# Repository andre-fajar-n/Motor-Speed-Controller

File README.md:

# motor-speed-controller
This is my answer for job test for Electrical Embedded Engineer position from a company. The task is to make motor speed controller used ATMega 328, and trasnfer the data to ESP wroom 02 to save in microSD card and web server

# Schematic Design
 
Or you can see the PDF in folder `Schematic`

# PCB Design
### Design for all layer

### Design for top layer

### Design for bottom layer

# Firmware
For firmware, I used Arduino programming to both of the microcontroller

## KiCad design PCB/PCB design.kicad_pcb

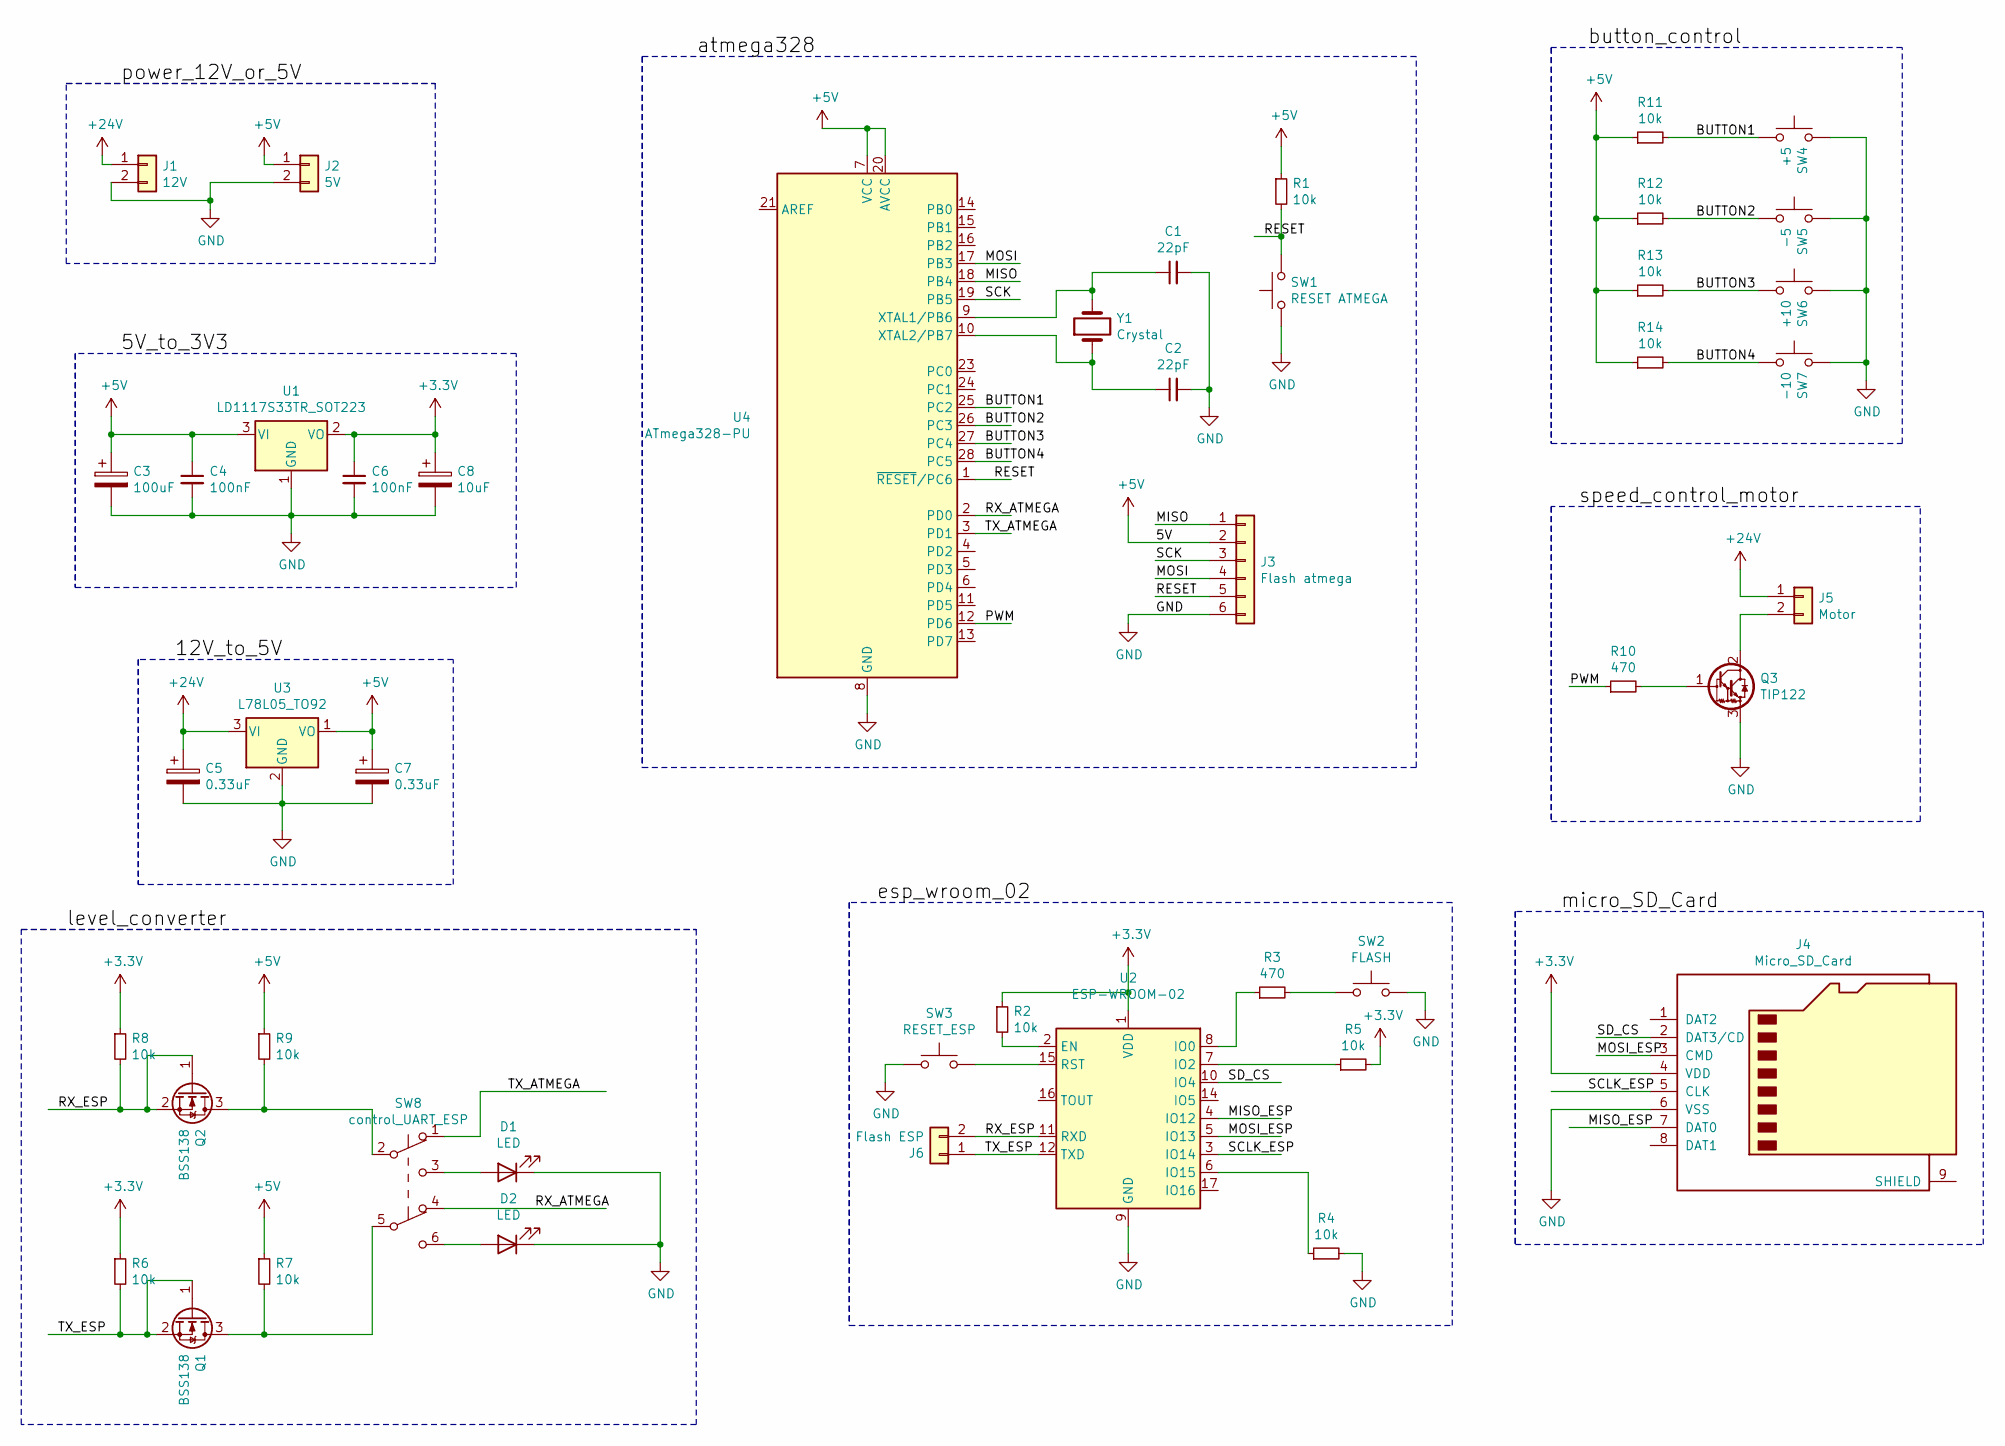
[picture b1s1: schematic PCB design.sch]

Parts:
C1, C2: 22pF; C_1210_3225Metric
C3: 100uF; CP_Elec_4x4.5
C4, C6: 100nF; C_1210_3225Metric
C5, C7: 0.33uF; CP_Elec_4x4.5
C8: 10uF; CP_Elec_4x4.5
D1, D2: LED; LED_0805_2012Metric
J1: 12V; PinSocket_1x02_P2.00mm_Vertical
J2: 5V; PinSocket_1x02_P2.00mm_Vertical
J3: Flash atmega; PinSocket_2x03_P2.00mm_Vertical
J4: Micro_SD_Card; microSD_HC_Hirose_DM3AT-SF-PEJM5
J5: Motor; PinHeader_1x02_P2.00mm_Vertical
J6: Flash ESP; PinHeader_1x02_P2.00mm_Vertical
Q1, Q2: BSS138; SOT-23
Q3: TIP122; TO-220-3_Vertical
R1, R2, R4, R5, R6, R7, R8, R9, R11, R12, R13, R14: 10k; R_0805_2012Metric
R3, R10: 470; R_0805_2012Metric
SW1: RESET ATMEGA; SW_Push_1P1T_NO_6x6mm_H9.5mm
SW2: FLASH; SW_Push_1P1T_NO_6x6mm_H9.5mm
SW3: RESET_ESP; SW_Push_1P1T_NO_6x6mm_H9.5mm
SW4: +5; SW_Push_1P1T_NO_6x6mm_H9.5mm
SW5: -5; SW_Push_1P1T_NO_6x6mm_H9.5mm
SW6: +10; SW_Push_1P1T_NO_6x6mm_H9.5mm
SW7: -10; SW_Push_1P1T_NO_6x6mm_H9.5mm
SW8: control_UART_ESP; SW_CuK_JS202011CQN_DPDT_Straight
U1: LD1117S33TR_SOT223; SOT-223-3_TabPin2
U2: ESP-WROOM-02
U3: L78L05_TO92; TO-92_Inline
U4: ATmega328-PU; DIP-28_W7.62mm
Y1: Crystal; Crystal_HC52-6mm_Vertical

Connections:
+3V3: C6.1, C8.1, J4.4 (VDD), R2.1, R5.2, R6.1, R8.1, U1.2 (VO), U2.1 (VDD)
+5V: C3.1, C4.1, C7.1, J2.1, J3.2, R1.1, R7.1, R9.1, R11.1, R12.1, R13.1, R14.1, U1.3 (VI), U3.1 (VO), U4.7 (VCC), U4.20 (AVCC)
+24V: C5.1, J1.1, J5.1, U3.3 (VI)
/BUTTON1: R11.2, SW4.1, U4.25 (PC2)
/BUTTON2: R12.2, SW5.1, U4.26 (PC3)
/BUTTON3: R13.2, SW6.1, U4.27 (PC4)
/BUTTON4: R14.2, SW7.1, U4.28 (PC5)
/MISO: J3.1, U4.18 (PB4)
/MISO_ESP: J4.7 (DAT0), U2.4 (IO12)
/MOSI: J3.4, U4.17 (PB3)
/MOSI_ESP: J4.3 (CMD), U2.5 (IO13)
/PWM: R10.1, U4.12 (PD6)
/RESET: J3.5, R1.2, SW1.2, U4.1 (~RESET~/PC6)
/RX_ATMEGA: SW8.4 (A), U4.2 (PD0)
/RX_ESP: J6.2, Q2.1 (G), Q2.2 (S), R8.2, U2.11 (RXD)
/SCK: J3.3, U4.19 (PB5)
/SCLK_ESP: J4.5 (CLK), U2.3 (IO14)
/SD_CS: J4.2 (DAT3/CD), U2.10 (IO4)
/TX_ATMEGA: SW8.1 (A), U4.3 (PD1)
/TX_ESP: J6.1, Q1.1 (G), Q1.2 (S), R6.2, U2.12 (TXD)
GND: C1.2, C2.2, C3.2, C4.2, C5.2, C6.2, C7.2, C8.2, D1.1 (K), D2.1 (K), J1.2, J2.2, J3.6, J4.6 (VSS), Q3.3 (E), R4.2, SW1.1, SW2.2, SW3.1, SW4.2, SW5.2, SW6.2, SW7.2, U1.1 (GND), U2.9 (GND), U2.13 (GND), U2.18 (GND), U2.19 (GND), U3.2 (GND), U4.8 (GND), U4.22 (GND)
unnamed: C1.1, U4.9 (XTAL1/PB6), Y1.2
unnamed: C2.1, U4.10 (XTAL2/PB7), Y1.1
unnamed: D1.2 (A), SW8.3 (C)
unnamed: D2.2 (A), SW8.6 (C)
unnamed: J5.2, Q3.2 (C)
unnamed: Q1.3 (D), R7.2, SW8.5 (B)
unnamed: Q2.3 (D), R9.2, SW8.2 (B)
unnamed: Q3.1 (B), R10.2
unnamed: R2.2, U2.2 (EN)
unnamed: R3.1, U2.8 (IO0)
unnamed: R3.2, SW2.1
unnamed: R4.1, U2.6 (IO15)
unnamed: R5.1, U2.7 (IO2)
unnamed: SW3.2, U2.15 (RST)

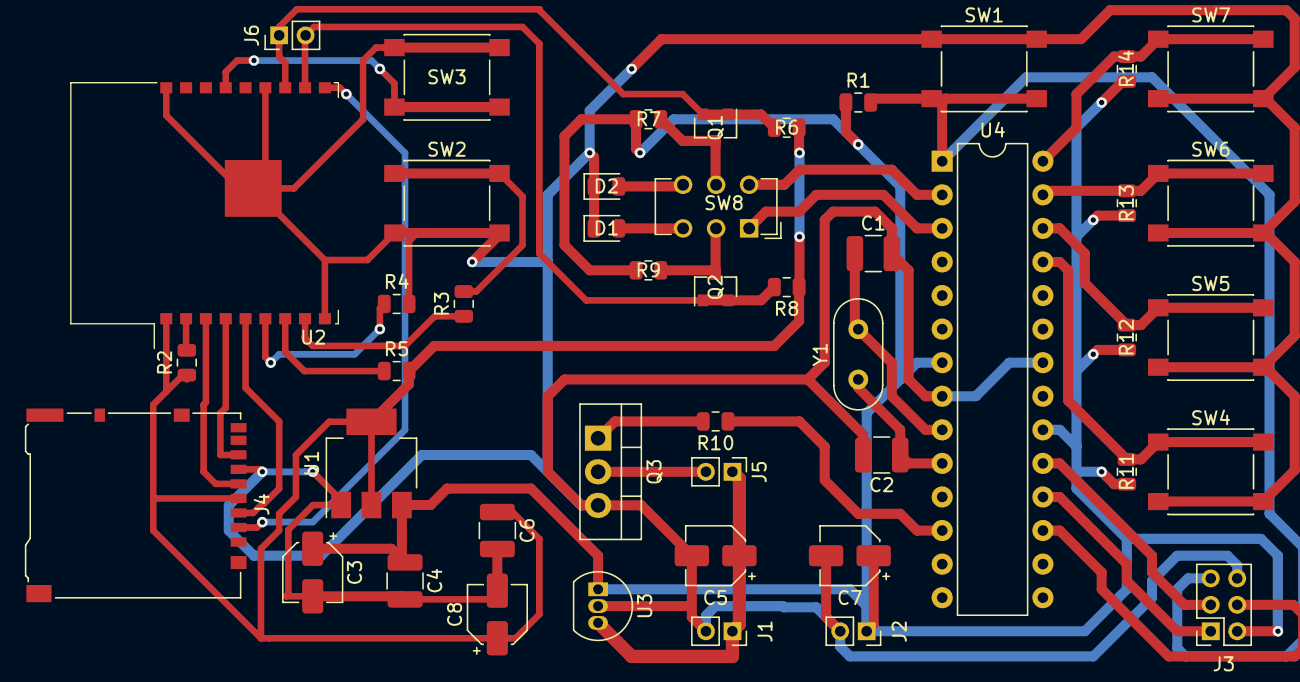
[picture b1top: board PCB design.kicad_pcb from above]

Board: 2 copper layers, 46 parts (0 on the bottom side), 35 nets.

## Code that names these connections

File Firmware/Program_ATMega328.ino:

const int button1 = A2; //pin 25 (+5 pwm)
const int button2 = A3; //pin 26 (-5 pwm)
const int button3 = A4; //pin 27 (+10 pwm)
const int button4 = A5; //pin 28 (-10 pwm)
const int pwm = 6; //pin 12

int buttonState1 = 0, buttonState2 = 0, buttonState3 = 0, buttonState4 = 0;
int lastButtonState1 = 0, lastButtonState2 = 0, lastButtonState3 = 0, lastButtonState4 = 0;
int speedMotor = 0;

void setup() {
  // put your setup code here, to run once:
  pinMode(button1, INPUT);
  pinMode(button2, INPUT);
  pinMode(button3, INPUT);
  pinMode(button4, INPUT);
  pinMode(pwm, OUTPUT);
  
  Serial.begin(9600);
}

//read condition button
int pushButton(int button, int buttonState, int lastButtonState){
  buttonState = digitalRead(button);

  if (buttonState != lastButtonState){
    if (buttonState == HIGH){
      if (button == A2){
        return 5;
      } else if (button == A3){
        return -5;
      } else if (button == A3){
        return 10;
      } else {
        return -10;
      }
    }
    delay(50);
  }
  return 0;
}

void loop() {
  // increase/decrease speed motor
  speedMotor += pushButton(button1, buttonState1, lastButtonState1);
  speedMotor += pushButton(button2, buttonState2, lastButtonState2);
  speedMotor += pushButton(button3, buttonState3, lastButtonState3);
  speedMotor += pushButton(button4, buttonState4, lastButtonState4);

  if (speedMotor > 255) speedMotor = 255;
  if (speedMotor < 0) speedMotor = 0;

  analogWrite(pwm, speedMotor);

  Serial.println(speedMotor);
}

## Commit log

2020-09-30 add file-file
